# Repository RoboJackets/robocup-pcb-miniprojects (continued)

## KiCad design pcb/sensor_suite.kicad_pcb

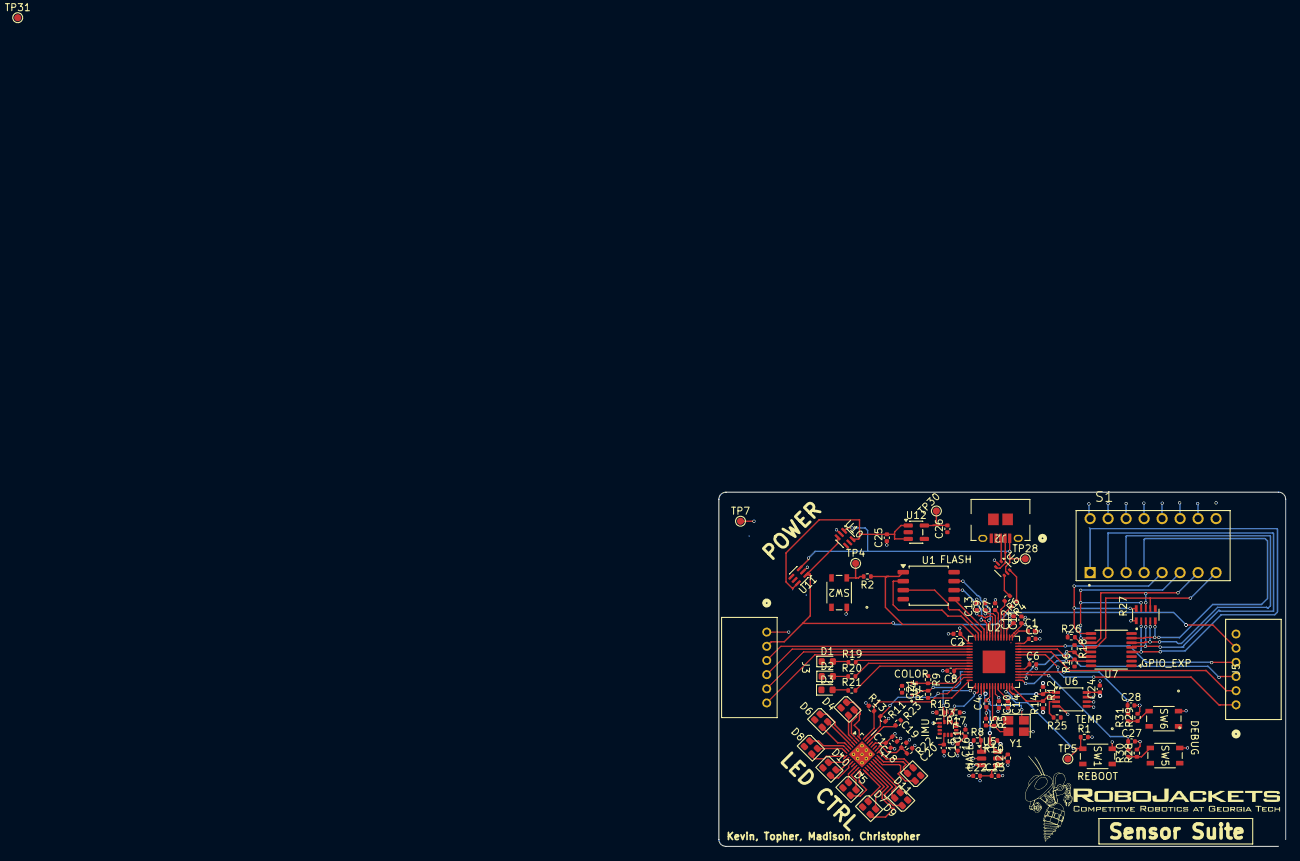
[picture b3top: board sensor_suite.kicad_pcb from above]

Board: 4 copper layers, 80.0 x 50.0 mm, 96 parts (0 on the bottom side), 91 nets.

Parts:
C1, C2, C3, C6, C7, C8, C9, C10, C13, C14, C27, C28: 100n; C_0402_1005Metric
C4, C5: 15p; C_0402_1005Metric
C11, C12, C18, C22, C25, C26: 1u; C_0402_1005Metric
C15: 10n; C_0402_1005Metric
C16: 2.2u; C_0402_1005Metric
C17, C19, C20, C21, C23, C24: 0.1u; C_0402_1005Metric
D1, D2, D3: RED; LED_0603_1608Metric
D4, D5, D6, D7, D8, D9, D10, D11: LED_RGB; LED_Cree-PLCC4_2x2mm_CW
IC1: IS31FL3254-QFLS4-TR; QFN-32-1EP_4x4mm_P0.4mm_EP2.65x2.65mm_ThermalVias
J2: USB_B_Micro; CONN_10118194-0001LF_AMP
J3, J5: Conn_01x06_Socket; CONN_S6B-PH-K-S_JST
R1, R28, R29, R30, R31: 10k; R_0402_1005Metric
R2, R5, R19, R20, R21: 1k; R_0402_1005Metric
R4, R6: 27.4; R_0402_1005Metric
R7, R8, R9, R10, R11, R12, R13, R14, R15, R16, R17, R18, R24, R25: 4.7k; R_0402_1005Metric
R22: 100k; R_0402_1005Metric
R23: 15k; R_0402_1005Metric
R26: 2k; R_0402_1005Metric
R27: YC158TJR-0710KL; RESCAXE64P320X160X70-10N
S1: DS01C-254-L-08BE; SW_DS01C-254-L-08BE
SW1, SW2, SW5, SW6: SKRPABE010; SW4_SKRPABE010_ALPS
TP4: ~{USB_Boot}; TestPoint_Pad_D1.0mm
TP5: ~{Reset}; TestPoint_Pad_D1.0mm
TP7: TestPoint; TestPoint_Pad_D1.0mm
TP28: +5V; TestPoint_Pad_D1.0mm
TP30: +3.3V; TestPoint_Pad_D1.0mm
TP31: VSPI; TestPoint_Pad_D1.0mm
U1: W25Q16JVSS; SOIC-8_5.3x5.3mm_P1.27mm
U2: RP2040; QFN-56-1EP_7x7mm_P0.4mm_EP3.2x3.2mm
U3: ICM-42605; LGA-14_3x2.5mm_P0.5mm_LayoutBorder3x4y
U4: VEML3328; SMD_L3328_VIS
U5: TMAG5273A2QDBV; SOT-23-6
U6: LM75ADP; TSSOP-8_3x3mm_P0.65mm
U7: TSSOP-16_4.4x5mm_P0.65mm
U9: USBLC6-2P6; SOT-666
U10, U11: LM66100DCK; SOT-363_SC-70-6
U12: AP2112K-3.3; SOT-23-5
Y1: ABM8-272-T3; Crystal_SMD_Abracon_ABM8AIG-4Pin_3.2x2.5mm

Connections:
+1.1V: C12.1, C13.1, C14.1, U2.23 (DVDD), U2.45 (VREG_VOUT), U2.50 (DVDD)
+3.3V: C1.1, C2.1, C3.1, C6.1, C7.1, C8.1, C9.1, C10.1, C11.1, C15.1, C16.1, C17.1, C21.1, C22.2, C23.1, C24.1, C26.2, D4.4 (BA), D5.4 (BA), D6.4 (BA), D7.4 (BA), D8.4 (BA), D9.4 (BA), D10.4 (BA), D11.4 (BA), R1.2, R7.1, R8.1, R9.1, R10.1, R11.1, R12.1, R13.1, R14.1, R15.1, R16.1, R17.1, R18.1, R24.1, R25.1, R26.1, R27.1, SW5.1 (A), SW6.1 (A), TP30.1 (1_1), U1.8 (VCC), U2.1 (IOVDD), U2.10 (IOVDD), U2.22 (IOVDD), U2.33 (IOVDD), U2.42 (IOVDD), U2.43 (ADC_AVDD), U2.44 (VREG_VIN), U2.48 (USB_VDD), U2.49 (IOVDD), U3.5 (VDDIO), U3.8 (VDD), U3.12 (CS), U4.4 (VDD), U5.4 (VCC), U6.8 (+Vs), U7.16 (VCC), U12.5 (VOUT)
+5V: C18.1, C19.1, IC1.28 (VCC)
/Color Sensor/I2C.SCL: R9.2, U2.12 (GPIO9), U4.3 (SCL)
/Color Sensor/I2C.SDA: R7.2, U2.11 (GPIO8), U4.2 (SDA)
/GPIO Expander/I2C.SCL: R18.2, U2.30 (GPIO19), U7.14 (SCL)
/GPIO Expander/I2C.SDA: R16.2, U2.29 (GPIO18), U7.15 (SDA)
/GPIO Expander/P0_PIN: R27.2 (R1), S1.1A, U7.4 (P0)
/GPIO Expander/P1_PIN: R27.3 (R2), S1.2A, U7.5 (P1)
/GPIO Expander/P2_PIN: R27.4 (R3), S1.3A, U7.6 (P2)
/GPIO Expander/P3_PIN: R27.5 (R4), S1.4A, U7.7 (P3)
/GPIO Expander/P4_PIN: R27.10 (R8), S1.5A, U7.9 (P4)
/GPIO Expander/P5_PIN: R27.9 (R7), S1.6A, U7.10 (P5)
/GPIO Expander/P6_PIN: R27.8 (R6), S1.7A, U7.11 (P6)
/GPIO Expander/P7_PIN: R27.7 (R5), S1.8A, U7.12 (P7)
/Hall Effect Sensor/I2C.SCL: R10.2, U2.18 (GPIO15), U5.6 (SDA)
/Hall Effect Sensor/I2C.SDA: R8.2, U2.17 (GPIO14), U5.1 (SCL)
/IMU/I2C.SCL: R17.2, U2.16 (GPIO13), U3.13 (SCL)
/IMU/I2C.SDA: R15.2, U2.15 (GPIO12), U3.14 (SDA)
/Indicator LEDs/ind_led0: R19.2, U2.7 (GPIO5)
/Indicator LEDs/ind_led1: R20.2, U2.8 (GPIO6)
/Indicator LEDs/ind_led2: R21.2, U2.9 (GPIO7)
/LED Controller/I2C.SCL: IC1.32 (SCL), R13.2, U2.14 (GPIO11)
/LED Controller/I2C.SDA: IC1.31 (SDA), R11.2, U2.13 (GPIO10)
/LED Controller/LED1.B: D4.3 (BK), IC1.3 (OUT3_B1)
/LED Controller/LED1.G: D4.2 (GK), IC1.2 (OUT2_G1)
/LED Controller/LED1.R: D4.1 (RK), IC1.1 (OUT1_R1)
/LED Controller/LED2.B: D6.3 (BK), IC1.6 (OUT6_B2)
/LED Controller/LED2.G: D6.2 (GK), IC1.5 (OUT5_G2)
/LED Controller/LED2.R: D6.1 (RK), IC1.4 (OUT4_R2)
/LED Controller/LED3.B: D8.3 (BK), IC1.9 (OUT9_B3)
/LED Controller/LED3.G: D8.2 (GK), IC1.8 (OUT8_G3)
/LED Controller/LED3.R: D8.1 (RK), IC1.7 (OUT7_R3)
/LED Controller/LED4.B: D10.3 (BK), IC1.12 (OUT12_B4)
/LED Controller/LED4.G: D10.2 (GK), IC1.11 (OUT11_G4)
/LED Controller/LED4.R: D10.1 (RK), IC1.10 (OUT10_R4)
/LED Controller/LED5.B: D5.3 (BK), IC1.16 (OUT15_B5)
/LED Controller/LED5.G: D5.2 (GK), IC1.15 (OUT14_G5)
/LED Controller/LED5.R: D5.1 (RK), IC1.14 (OUT13_R5)
/LED Controller/LED6.B: D7.3 (BK), IC1.19 (OUT18_B6)
/LED Controller/LED6.G: D7.2 (GK), IC1.18 (OUT17_G6)
/LED Controller/LED6.R: D7.1 (RK), IC1.17 (OUT16_R6)
/LED Controller/LED7.B: D9.3 (BK), IC1.22 (OUT21_B7)
/LED Controller/LED7.G: D9.2 (GK), IC1.21 (OUT20_G7)
/LED Controller/LED7.R: D9.1 (RK), IC1.20 (OUT19_R7)
/LED Controller/LED8.B: D11.3 (BK), IC1.25 (OUT24_B8)
/LED Controller/LED8.G: D11.2 (GK), IC1.24 (OUT23_G8)
/LED Controller/LED8.R: D11.1 (RK), IC1.23 (OUT22_R8)
/MCU/I2C_TS.SCL: R14.2, U2.28 (GPIO17), U6.2 (SCL)
/MCU/I2C_TS.SDA: R12.2, U2.27 (GPIO16), U6.1 (SDA)
/MCU/QSPI_CLK: U1.6 (CLK), U2.52 (QSPI_SCLK)
/MCU/QSPI_SD0: U1.5 (DI/IO_{0}), U2.53 (QSPI_SD0)
/MCU/QSPI_SD1: U1.2 (DO/IO_{1}), U2.55 (QSPI_SD1)
/MCU/QSPI_SD2: U1.3 (~WP/IO_{2}), U2.54 (QSPI_SD2)
/MCU/QSPI_SD3: U1.7 (~HOLD/~RESET/IO_{3}), U2.51 (QSPI_SD3)
/MCU/gp_btn_a: C27.1, R30.2, U2.31 (GPIO20)
/MCU/gp_btn_b: C28.1, R31.2, U2.32 (GPIO21)
/MCU/~QSPI_CS: R2.1, U1.1 (~CS), U2.56 (~QSPI_SS)
/MCU/~RESET: R1.1, SW1.2 (B), TP5.1 (1_1), U2.26 (RUN)
/MCU/~USB_BOOT: R2.2, SW2.2 (B), TP4.1 (1_1)
/Power/VSPI: J3.2, J5.5, TP31.1 (1_1), U10.3 (~CE), U11.1 (VIN)
/SPI0.CSN: J3.6, U2.5 (GPIO3)
/SPI0.MISO: J3.4, U2.3 (GPIO1)
/SPI0.MOSI: J3.5, U2.4 (GPIO2)
/SPI0.SCK: J3.3, U2.2 (GPIO0)
/SPI1.CSN: J5.1, U2.38 (GPIO26/ADC0)
/SPI1.MISO: J5.3, U2.40 (GPIO28/ADC2)
/SPI1.MOSI: J5.2, U2.39 (GPIO27/ADC1)
/SPI1.SCK: J5.4, U2.41 (GPIO29/ADC3)
/USB.DM: R4.1, U9.6 (I/O1)
/USB.DP: R6.1, U9.4 (I/O2)
GND: C1.2, C2.2, C3.2, C4.1, C5.1, C6.2, C7.2, C8.2, C9.2, C10.2, C11.2, C12.2, C13.2, C14.2, C15.2, C16.2, C17.2, C18.2, C19.2, C20.2, C21.2, C22.1, C23.2, C24.2, C25.1, C26.1, C27.2, C28.2, D1.1 (K), D2.1 (K), D3.1 (K), IC1.13 (GND_1), IC1.27 (AD), IC1.29 (GND_2), J2.5 (GND), J3.1, J5.6, R22.2, R23.2, R28.2, R29.2, S1.1B, S1.2B, S1.3B, S1.4B, S1.5B, S1.6B, S1.7B, S1.8B, SW1.1 (A), SW2.1 (A), TP7.1 (1_1), U1.4 (GND), U2.19 (TESTEN), U2.57 (GND), U3.1 (AD0), U3.6 (GND), U4.1 (GND), U5.2 (GND), U5.3 (TEST), U6.4 (GND), U6.5 (A2), U6.6 (A1), U6.7 (A0), U7.1 (A0), U7.2 (A1), U7.3 (A2), U7.8 (GND), U9.2 (GND), U10.2 (GND), U11.2 (GND), U12.2 (GND), Y1.2 (G), Y1.4 (G)
unnamed: C5.2, R5.2, Y1.3
unnamed: D1.2 (A), R19.1
unnamed: D2.2 (A), R20.1
unnamed: D3.2 (A), R21.1
unnamed: IC1.30 (ISET), R23.1
unnamed: C20.1, IC1.26 (SDB), R22.1
unnamed: J2.3 (D+), U9.1 (I/O1)
unnamed: J2.2 (D-), U9.3 (I/O2)
unnamed: J2.1 (VBUS), TP28.1 (1_1), U9.5 (VBUS), U10.1 (VIN), U11.3 (~CE)
unnamed: R28.1, R30.1, SW5.2 (B)
unnamed: R29.1, R31.1, SW6.2 (B)
unnamed: R4.2, U2.46 (USB_DM)
unnamed: R6.2, U2.47 (USB_DP)
unnamed: C4.2, U2.20 (XIN), Y1.1
unnamed: R5.1, U2.21 (XOUT)
unnamed: R24.2, U5.5 (~INT)
unnamed: R25.2, U6.3 (O.S.)
unnamed: R26.2, U7.13 (~INT)
VBUS: C25.2, U10.6 (VOUT), U11.6 (VOUT), U12.1 (VIN), U12.3 (EN)

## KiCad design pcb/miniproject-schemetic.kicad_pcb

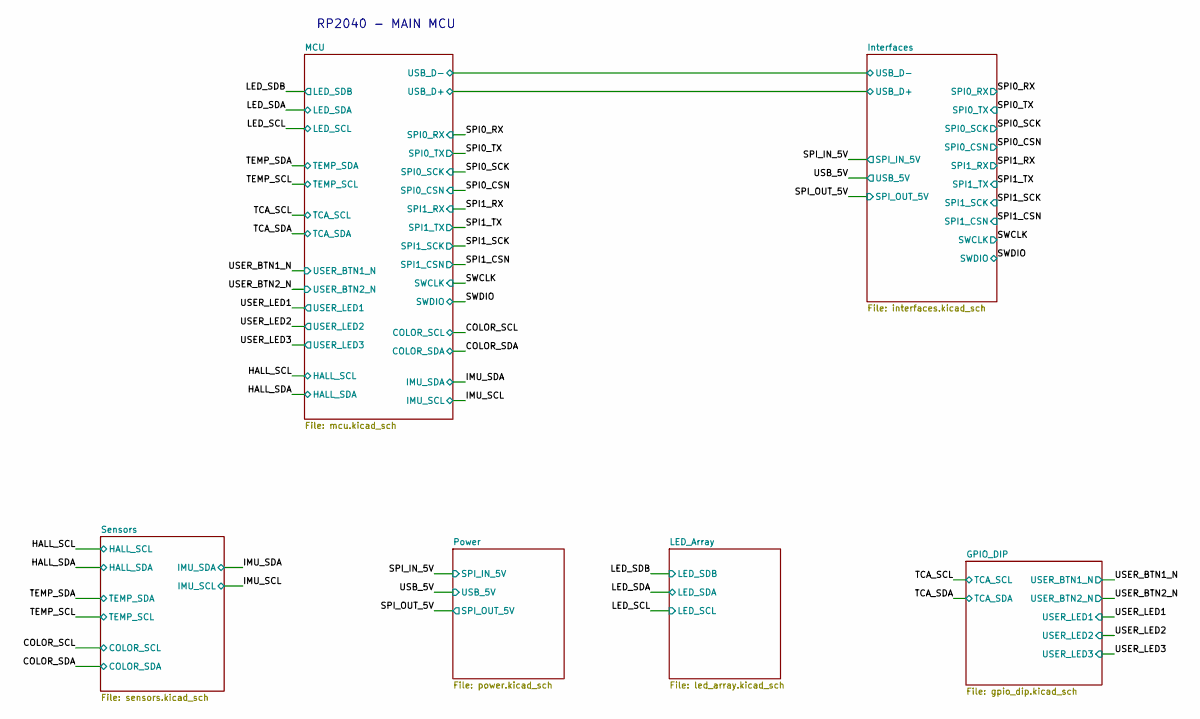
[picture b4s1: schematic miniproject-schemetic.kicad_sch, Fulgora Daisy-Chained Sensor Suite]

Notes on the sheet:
RP2040 - MAIN MCU

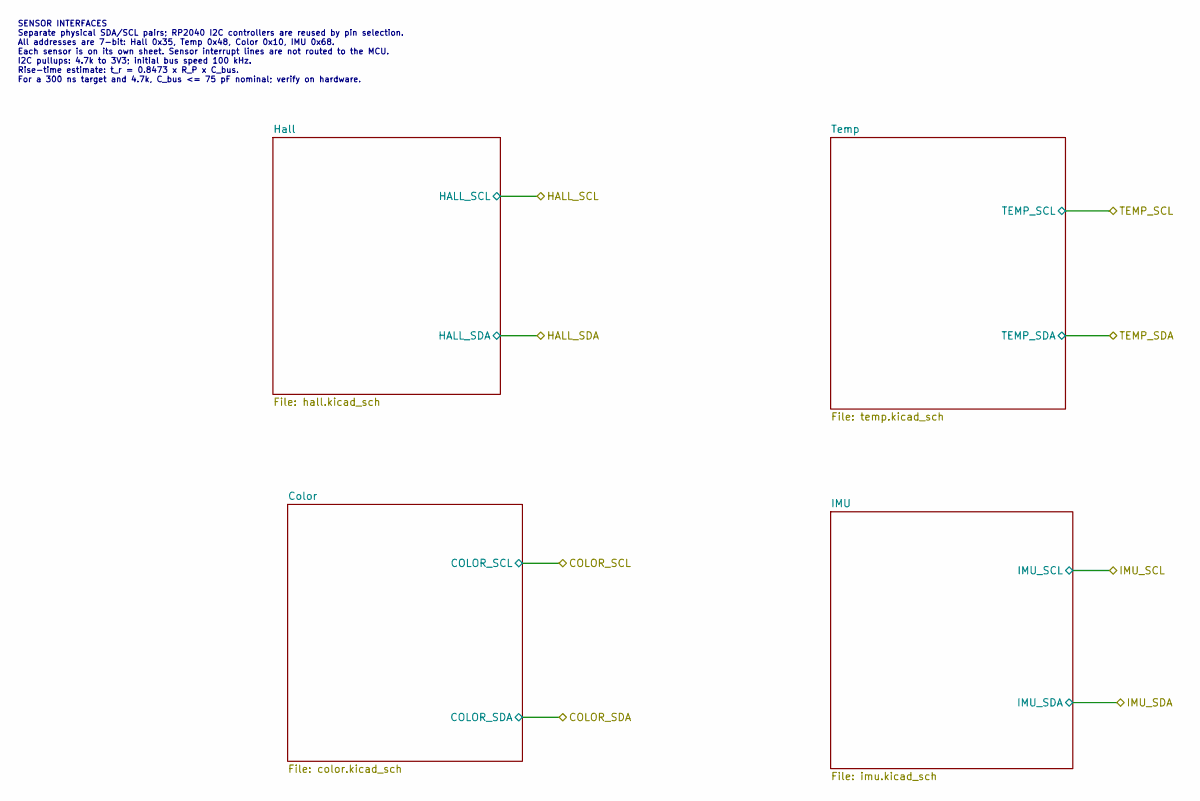
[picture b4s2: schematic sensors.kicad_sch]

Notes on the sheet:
SENSOR INTERFACES Separate physical SDA/SCL pairs; RP2040 I2C controllers are reused by pin selection. All addresses are 7-bit: Hall 0x35, Temp 0x48, Color 0x10, IMU 0x68. Each sensor is on its own sheet. Sensor interrupt lines are not routed to the MCU. I2C pullups: 4.7k to 3V3; initial bus speed 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

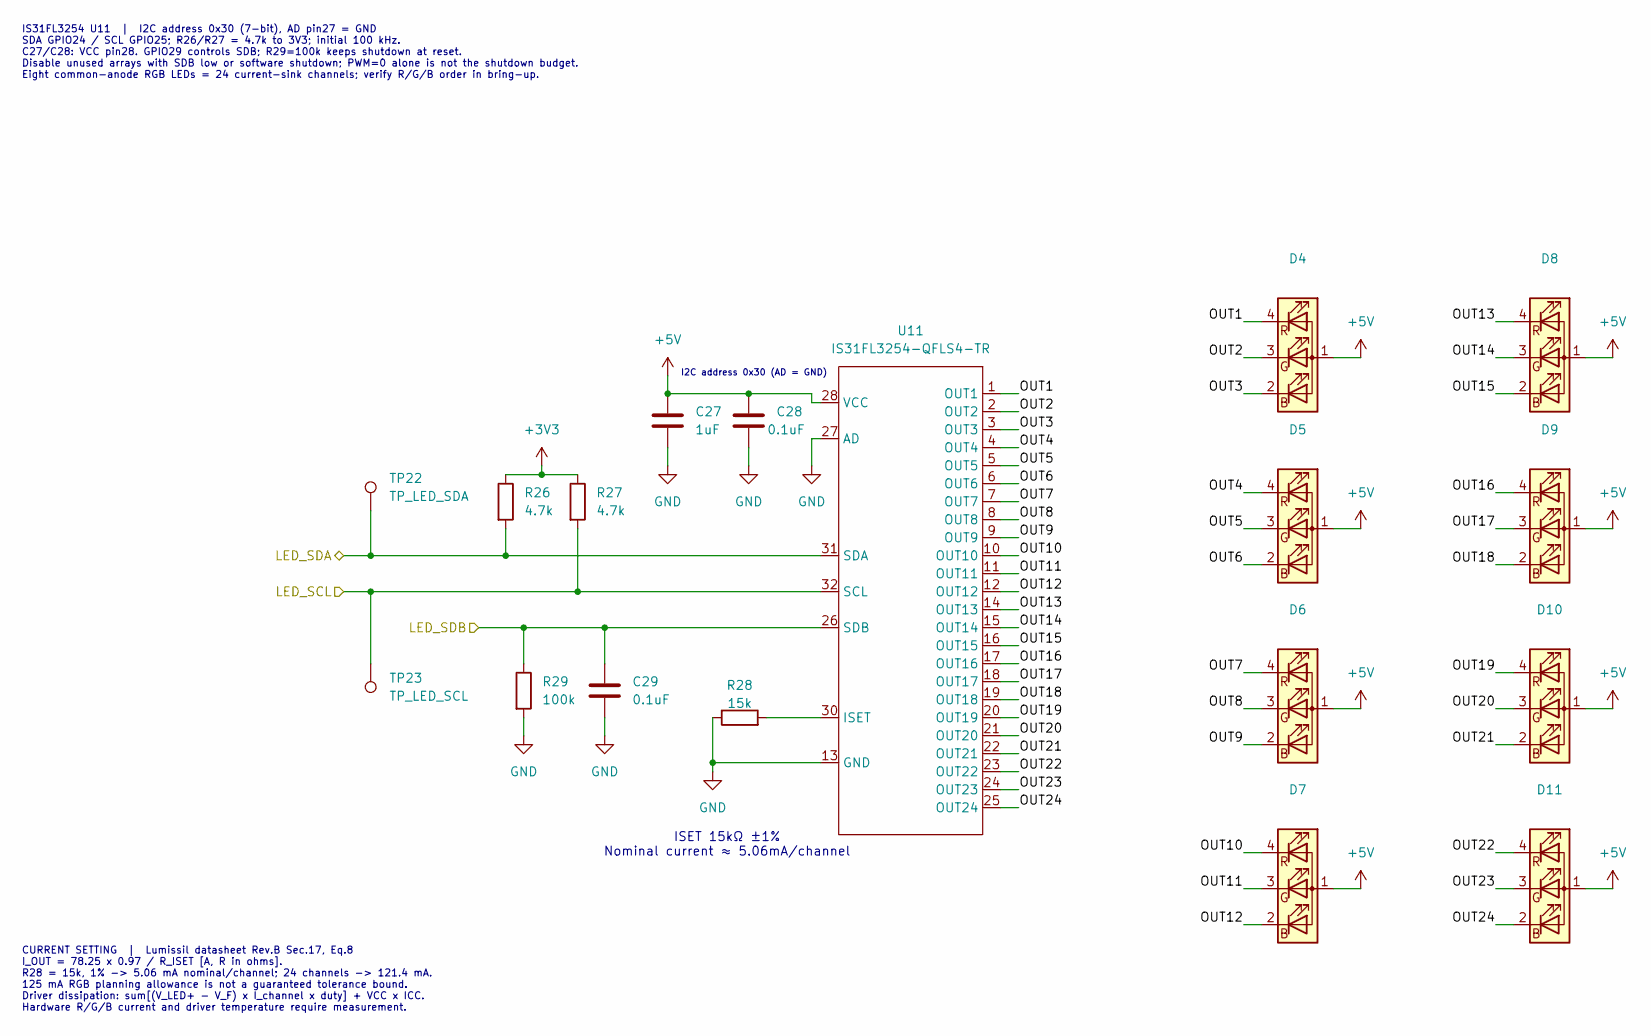
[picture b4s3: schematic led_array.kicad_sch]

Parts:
C27: 1uF; C_0603_1608Metric; Tolerance 10%; Voltage 10V minimum
C28: 0.1uF; C_0603_1608Metric; Tolerance 10%; Voltage 10V minimum
C29: 0.1uF; C_0603_1608Metric; Tolerance 10%; Voltage 6.3V minimum
D4, D5, D6, D7, D8, D9, D10, D11: CLMVC-FKA-CL1D1L71BB7C3C3; LED_Cree-PLCC4_2x2mm_CW
R26, R27: 4.7k; R_0603_1608Metric; Tolerance 1%
R28: 15k; R_0603_1608Metric; Tolerance 1%
R29: 100k; R_0603_1608Metric; Tolerance 1%
TP22: TP_LED_SDA; TestPoint_Pad_D1.0mm
TP23: TP_LED_SCL; TestPoint_Pad_D1.0mm
U11: IS31FL3254-QFLS4-TR; VQFN-32-1EP_4x4mm_P0.4mm_EP2.8x2.8mm

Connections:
+3V3: R26.1, R27.1; also elsewhere on the board
+5V: C27.1, C28.1, D4.1 (A), D5.1 (A), D6.1 (A), D7.1 (A), D8.1 (A), D9.1 (A), D10.1 (A), D11.1 (A), U11.28 (VCC); also elsewhere on the board
/LED_Array/OUT1: D4.4 (RK), U11.1 (OUT1)
/LED_Array/OUT2: D4.3 (GK), U11.2 (OUT2)
/LED_Array/OUT3: D4.2 (BK), U11.3 (OUT3)
/LED_Array/OUT4: D5.4 (RK), U11.4 (OUT4)
/LED_Array/OUT5: D5.3 (GK), U11.5 (OUT5)
/LED_Array/OUT6: D5.2 (BK), U11.6 (OUT6)
/LED_Array/OUT7: D6.4 (RK), U11.7 (OUT7)
/LED_Array/OUT8: D6.3 (GK), U11.8 (OUT8)
/LED_Array/OUT9: D6.2 (BK), U11.9 (OUT9)
/LED_Array/OUT10: D7.4 (RK), U11.10 (OUT10)
/LED_Array/OUT11: D7.3 (GK), U11.11 (OUT11)
/LED_Array/OUT12: D7.2 (BK), U11.12 (OUT12)
/LED_Array/OUT13: D8.4 (RK), U11.14 (OUT13)
/LED_Array/OUT14: D8.3 (GK), U11.15 (OUT14)
/LED_Array/OUT15: D8.2 (BK), U11.16 (OUT15)
/LED_Array/OUT16: D9.4 (RK), U11.17 (OUT16)
/LED_Array/OUT17: D9.3 (GK), U11.18 (OUT17)
/LED_Array/OUT18: D9.2 (BK), U11.19 (OUT18)
/LED_Array/OUT19: D10.4 (RK), U11.20 (OUT19)
/LED_Array/OUT20: D10.3 (GK), U11.21 (OUT20)
/LED_Array/OUT21: D10.2 (BK), U11.22 (OUT21)
/LED_Array/OUT22: D11.4 (RK), U11.23 (OUT22)
/LED_Array/OUT23: D11.3 (GK), U11.24 (OUT23)
/LED_Array/OUT24: D11.2 (BK), U11.25 (OUT24)
/LED_SCL: R27.2, TP23.1 (1_1), U11.32 (SCL); also elsewhere on the board
/LED_SDA: R26.2, TP22.1 (1_1), U11.31 (SDA); also elsewhere on the board
/LED_SDB: C29.1, R29.1, U11.26 (SDB); also elsewhere on the board
GND: C27.2, C28.2, C29.2, R28.1, R29.2, U11.13 (GND), U11.27 (AD), U11.29 (GND), U11.33 (GND_(pad)); also elsewhere on the board
unnamed: R28.2, U11.30 (ISET)

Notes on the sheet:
I2C address 0x30 (AD = GND)
ISET 15kΩ ±1% Nominal current ≈ 5.06mA/channel
IS31FL3254 U11 | I2C address 0x30 (7-bit), AD pin27 = GND SDA GPIO24 / SCL GPIO25; R26/R27 = 4.7k to 3V3; initial 100 kHz. C27/C28: VCC pin28. GPIO29 controls SDB; R29=100k keeps shutdown at reset. Disable unused arrays with SDB low or software shutdown; PWM=0 alone is not the shutdown budget. Eigh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
CURRENT SETTING | Lumissil datasheet Rev.B Sec.17, Eq.8 I_OUT = 78.25 x 0.97 / R_ISET [A, R in ohms]. R28 = 15k, 1% -> 5.06 mA nominal/channel; 24 channels -> 121.4 mA. 125 mA RGB planning allowance is not a guaranteed tolerance bound. Driver dissipation: sum[(V_LED+ - V_F) x I_channel x duty] + VC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

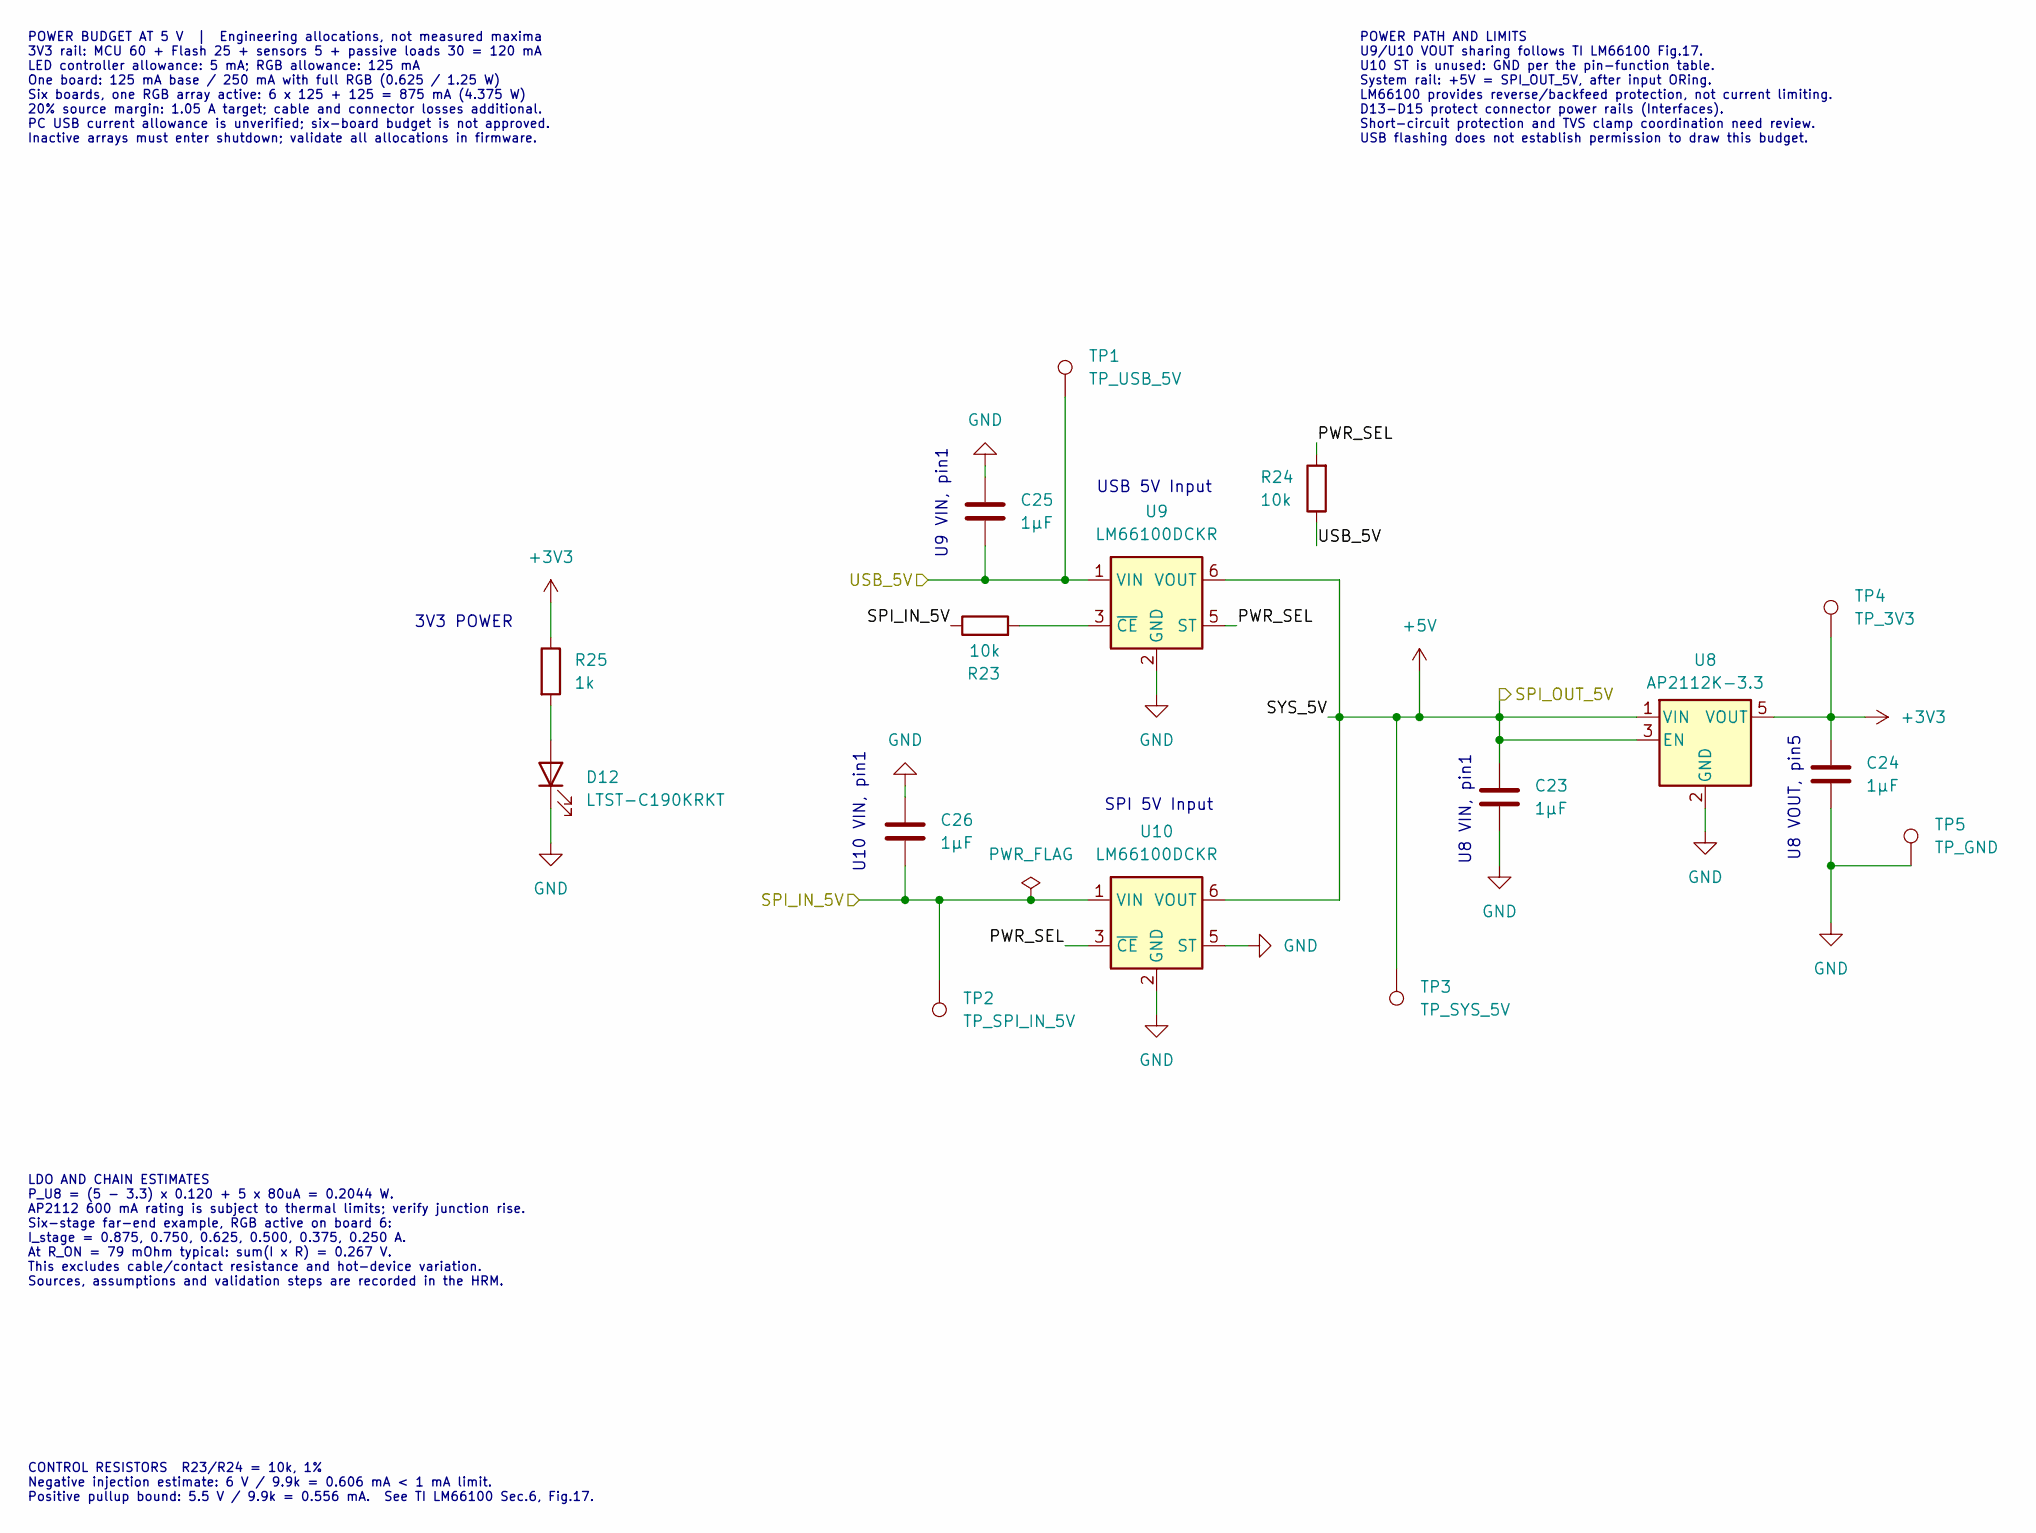
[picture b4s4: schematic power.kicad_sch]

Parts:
C23, C25, C26: 1µF; C_0603_1608Metric; Tolerance 10%; Voltage 10V minimum
C24: 1µF; C_0603_1608Metric; Tolerance 10%; Voltage 6.3V minimum
D12: LTST-C190KRKT; LED_0603_1608Metric
R23, R24: 10k; R_0603_1608Metric; Tolerance 1%
R25: 1k; R_0603_1608Metric; Tolerance 1%
TP1: TP_USB_5V; TestPoint_Pad_D1.0mm
TP2: TP_SPI_IN_5V; TestPoint_Pad_D1.0mm
TP3: TP_SYS_5V; TestPoint_Pad_D1.0mm
TP4: TP_3V3; TestPoint_Pad_D1.0mm
TP5: TP_GND; TestPoint_Pad_D1.0mm
U8: AP2112K-3.3; SOT-23-5
U9, U10: LM66100DCKR; SOT-363_SC-70-6

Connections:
+3V3: C24.1, R25.1, TP4.1 (1_1), U8.5 (VOUT); also elsewhere on the board
+5V: C23.1, TP3.1 (1_1), U8.1 (VIN), U8.3 (EN), U9.6 (VOUT), U10.6 (VOUT); also elsewhere on the board
/Power/PWR_SEL: R24.2, U9.5 (ST), U10.3 (~CE)
/SPI_IN_5V: C26.2, R23.1, TP2.1 (1_1), U10.1 (VIN); also elsewhere on the board
/USB_5V: C25.2, R24.1, TP1.1 (1_1), U9.1 (VIN); also elsewhere on the board
GND: C23.2, C24.2, C25.1, C26.1, D12.1 (K), TP5.1 (1_1), U8.2 (GND), U9.2 (GND), U10.2 (GND), U10.5 (ST); also elsewhere on the board
unnamed: D12.2 (A), R25.2
unnamed: R23.2, U9.3 (~CE)

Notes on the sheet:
3V3 POWER
SPI 5V Input
USB 5V Input
U9 VIN, pin1
U8 VOUT, pin5
U8 VIN, pin1
U10 VIN, pin1
POWER BUDGET AT 5 V | Engineering allocations, not measured maxima 3V3 rail: MCU 60 + Flash 25 + sensors 5 + passive loads 30 = 120 mA LED controller allowance: 5 mA; RGB allowance: 125 mA One board: 125 mA base / 250 mA with full RGB (0.625 / 1.25 W) Six boards, one RGB array active: 6 x 125 + 125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
POWER PATH AND LIMITS U9/U10 VOUT sharing follows TI LM66100 Fig.17. U10 ST is unused: GND per the pin-function table. System rail: +5V = SPI_OUT_5V, after input ORing. LM66100 provides reverse/backfeed protection, not current limiting. D13-D15 protect connector power rails (Interfaces). Short-circ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
LDO AND CHAIN ESTIMATES P_U8 = (5 - 3.3) x 0.120 + 5 x 80uA = 0.2044 W. AP2112 600 mA rating is subject to thermal limits; verify junction rise. Six-stage far-end example, RGB active on board 6: I_stage = 0.875, 0.750, 0.625, 0.500, 0.375, 0.250 A. At R_ON = 79 mOhm typical: sum(I x R) = 0.267 V. T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
CONTROL RESISTORS R23/R24 = 10k, 1% Negative injection estimate: 6 V / 9.9k = 0.606 mA < 1 mA limit. Positive pullup bound: 5.5 V / 9.9k = 0.556 mA. See TI LM66100 Sec.6, Fig.17.

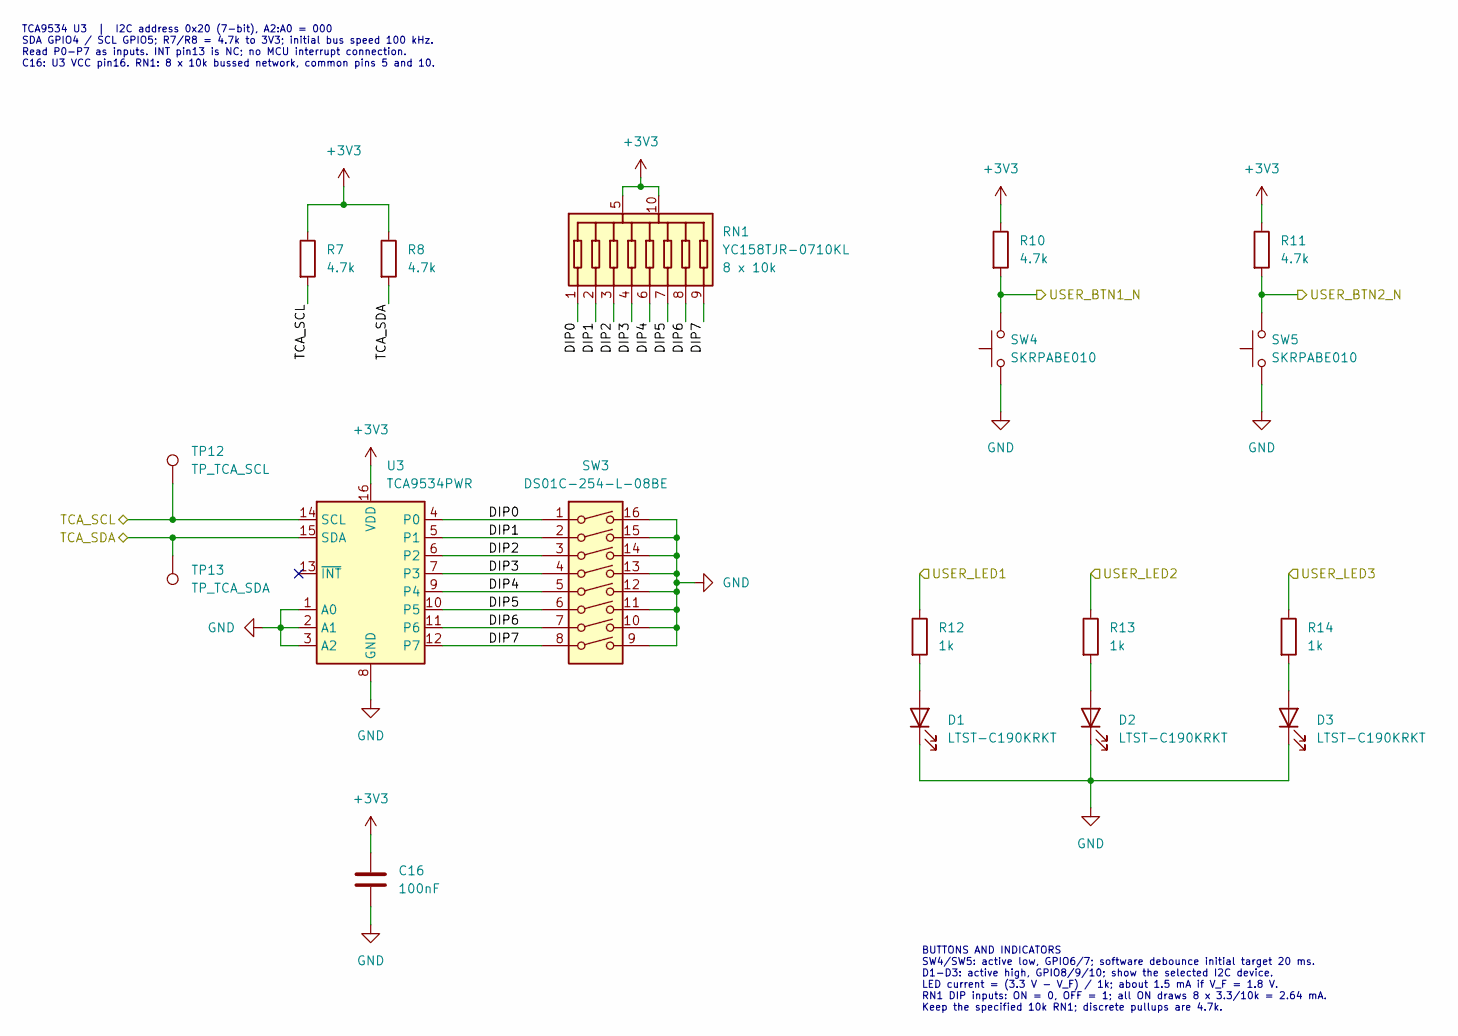
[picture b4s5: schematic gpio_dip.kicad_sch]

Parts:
C16: 100nF; C_0603_1608Metric; Tolerance 10%; Voltage 6.3V minimum
D1, D2, D3: LTST-C190KRKT; LED_0603_1608Metric
R7, R8, R10, R11: 4.7k; R_0603_1608Metric; Tolerance 1%
R12, R13, R14: 1k; R_0603_1608Metric; Tolerance 1%
RN1: YC158TJR-0710KL; Yageo_YC158T_10Pin_3.2x1.6mm_P0.64mm; Tolerance 5%
SW3: DS01C-254-L-08BE; SW_DIP_SPSTx08_SameSky_DS01C-254-L-08BE
SW4, SW5: SKRPABE010; SW_SPST_ALPS_SKRPABE010_4.2x3.2mm
TP12: TP_TCA_SCL; TestPoint_Pad_D1.0mm
TP13: TP_TCA_SDA; TestPoint_Pad_D1.0mm
U3: TCA9534PWR; TSSOP-16_4.4x5mm_P0.65mm

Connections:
+3V3: C16.1, R7.1, R8.1, R10.1, R11.1, RN1.5 (COM), RN1.10 (COM), U3.16 (VDD); also elsewhere on the board
/GPIO_DIP/DIP0: RN1.1 (R1), SW3.1, U3.4 (P0)
/GPIO_DIP/DIP1: RN1.2 (R2), SW3.2, U3.5 (P1)
/GPIO_DIP/DIP2: RN1.3 (R3), SW3.3, U3.6 (P2)
/GPIO_DIP/DIP3: RN1.4 (R4), SW3.4, U3.7 (P3)
/GPIO_DIP/DIP4: RN1.6 (R5), SW3.5, U3.9 (P4)
/GPIO_DIP/DIP5: RN1.7 (R6), SW3.6, U3.10 (P5)
/GPIO_DIP/DIP6: RN1.8 (R7), SW3.7, U3.11 (P6)
/GPIO_DIP/DIP7: RN1.9 (R8), SW3.8, U3.12 (P7)
/TCA_SCL: R7.2, TP12.1 (1_1), U3.14 (SCL); also elsewhere on the board
/TCA_SDA: R8.2, TP13.1 (1_1), U3.15 (SDA); also elsewhere on the board
/USER_BTN1_N: R10.2, SW4.2; also elsewhere on the board
/USER_BTN2_N: R11.2, SW5.2; also elsewhere on the board
/USER_LED1: R12.1; also elsewhere on the board
/USER_LED2: R13.1; also elsewhere on the board
/USER_LED3: R14.1; also elsewhere on the board
GND: C16.2, D1.1 (K), D2.1 (K), D3.1 (K), SW3.9, SW3.10, SW3.11, SW3.12, SW3.13, SW3.14, SW3.15, SW3.16, SW4.1, SW5.1, U3.1 (A0), U3.2 (A1), U3.3 (A2), U3.8 (GND); also elsewhere on the board
unnamed: D1.2 (A), R12.2
unnamed: D2.2 (A), R13.2
unnamed: D3.2 (A), R14.2

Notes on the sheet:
TCA9534 U3 | I2C address 0x20 (7-bit), A2:A0 = 000 SDA GPIO4 / SCL GPIO5; R7/R8 = 4.7k to 3V3; initial bus speed 100 kHz. Read P0-P7 as inputs. INT pin13 is NC; no MCU interrupt connection. C16: U3 VCC pin16. RN1: 8 x 10k bussed network, common pins 5 and 10.
BUTTONS AND INDICATORS SW4/SW5: active low, GPIO6/7; software debounce initial target 20 ms. D1-D3: active high, GPIO8/9/10; show the selected I2C device. LED current = (3.3 V - V_F) / 1k; about 1.5 mA if V_F = 1.8 V. RN1 DIP inputs: ON = 0, OFF = 1; all ON draws 8 x 3.3/10k = 2.64 mA. Keep the spe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

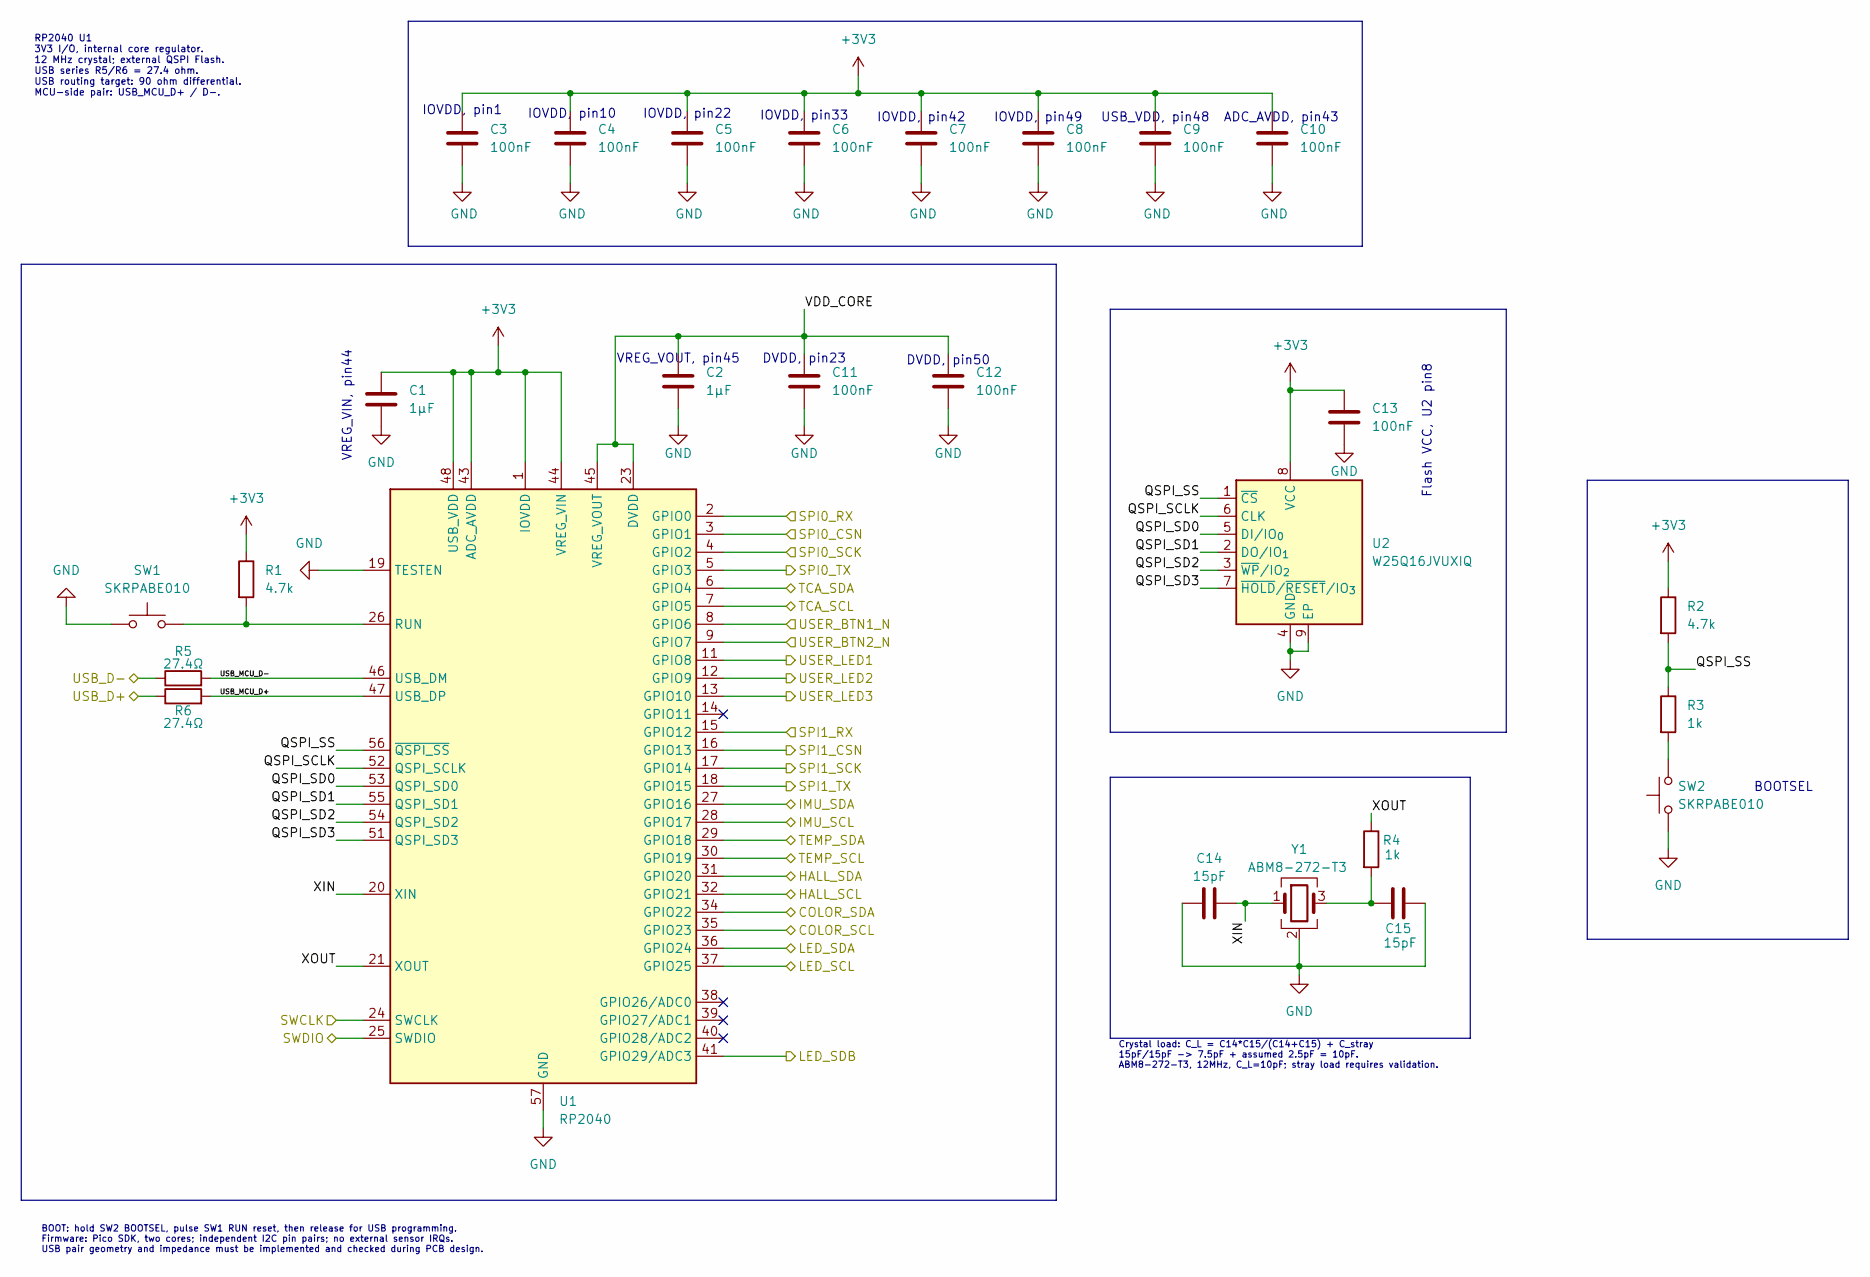
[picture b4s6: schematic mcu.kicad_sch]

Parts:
C1, C2: 1µF; C_0603_1608Metric; Tolerance 10%; Voltage 6.3V minimum
C3, C4, C5, C6, C7, C8, C9, C10, C11, C12, C13: 100nF; C_0603_1608Metric; Tolerance 10%; Voltage 6.3V minimum
C14, C15: 15pF; C_0603_1608Metric; Tolerance 5%; Voltage 6.3V minimum
R1, R2: 4.7k; R_0603_1608Metric; Tolerance 1%
R3, R4: 1k; R_0603_1608Metric; Tolerance 1%
R5, R6: 27.4Ω; R_0603_1608Metric; Tolerance 1%
SW1, SW2: SKRPABE010; SW_SPST_ALPS_SKRPABE010_4.2x3.2mm
U1: RP2040; QFN-56-1EP_7x7mm_P0.4mm_EP3.2x3.2mm
U2: W25Q16JVUXIQ; Winbond_USON-8-1EP_3x2mm_P0.5mm_EP0.2x1.6mm
Y1: ABM8-272-T3; Crystal_SMD_3225-4Pin_3.2x2.5mm

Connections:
+3V3: C1.1, C3.1, C4.1, C5.1, C6.1, C7.1, C8.1, C9.1, C10.1, C13.1, R1.1, R2.1, U1.1 (IOVDD), U1.10 (IOVDD), U1.22 (IOVDD), U1.33 (IOVDD), U1.42 (IOVDD), U1.43 (ADC_AVDD), U1.44 (VREG_VIN), U1.48 (USB_VDD), U1.49 (IOVDD), U2.8 (VCC); also elsewhere on the board
/COLOR_SCL: U1.35 (GPIO23); also elsewhere on the board
/COLOR_SDA: U1.34 (GPIO22); also elsewhere on the board
/HALL_SCL: U1.32 (GPIO21); also elsewhere on the board
/HALL_SDA: U1.31 (GPIO20); also elsewhere on the board
/IMU_SCL: U1.28 (GPIO17); also elsewhere on the board
/IMU_SDA: U1.27 (GPIO16); also elsewhere on the board
/Interfaces/USB_D+: R6.1; also elsewhere on the board
/Interfaces/USB_D-: R5.1; also elsewhere on the board
/LED_SCL: U1.37 (GPIO25); also elsewhere on the board
/LED_SDA: U1.36 (GPIO24); also elsewhere on the board
/LED_SDB: U1.41 (GPIO29/ADC3); also elsewhere on the board
/MCU/QSPI_SCLK: U1.52 (QSPI_SCLK), U2.6 (CLK)
/MCU/QSPI_SD0: U1.53 (QSPI_SD0), U2.5 (DI/IO_{0})
/MCU/QSPI_SD1: U1.55 (QSPI_SD1), U2.2 (DO/IO_{1})
/MCU/QSPI_SD2: U1.54 (QSPI_SD2), U2.3 (~WP/IO_{2})
/MCU/QSPI_SD3: U1.51 (QSPI_SD3), U2.7 (~HOLD/~RESET/IO_{3})
/MCU/QSPI_SS: R2.2, R3.1, U1.56 (~QSPI_SS), U2.1 (~CS)
/MCU/USB_MCU_D+: R6.2, U1.47 (USB_DP)
/MCU/USB_MCU_D-: R5.2, U1.46 (USB_DM)
/MCU/VDD_CORE: C2.1, C11.1, C12.1, U1.23 (DVDD), U1.45 (VREG_VOUT), U1.50 (DVDD)
/MCU/XIN: C14.2, U1.20 (XIN), Y1.1
/MCU/XOUT: R4.1, U1.21 (XOUT)
/SPI0_CSN: U1.3 (GPIO1); also elsewhere on the board
/SPI0_RX: U1.2 (GPIO0); also elsewhere on the board
/SPI0_SCK: U1.4 (GPIO2); also elsewhere on the board
/SPI0_TX: U1.5 (GPIO3); also elsewhere on the board
/SPI1_CSN: U1.16 (GPIO13); also elsewhere on the board
/SPI1_RX: U1.15 (GPIO12); also elsewhere on the board
/SPI1_SCK: U1.17 (GPIO14); also elsewhere on the board
/SPI1_TX: U1.18 (GPIO15); also elsewhere on the board
/SWCLK: U1.24 (SWCLK); also elsewhere on the board
/SWDIO: U1.25 (SWDIO); also elsewhere on the board
/TCA_SCL: U1.7 (GPIO5); also elsewhere on the board
/TCA_SDA: U1.6 (GPIO4); also elsewhere on the board
/TEMP_SCL: U1.30 (GPIO19); also elsewhere on the board
/TEMP_SDA: U1.29 (GPIO18); also elsewhere on the board
/USER_BTN1_N: U1.8 (GPIO6); also elsewhere on the board
/USER_BTN2_N: U1.9 (GPIO7); also elsewhere on the board
/USER_LED1: U1.11 (GPIO8); also elsewhere on the board
/USER_LED2: U1.12 (GPIO9); also elsewhere on the board
/USER_LED3: U1.13 (GPIO10); also elsewhere on the board
GND: C1.2, C2.2, C3.2, C4.2, C5.2, C6.2, C7.2, C8.2, C9.2, C10.2, C11.2, C12.2, C13.2, C14.1, C15.2, SW1.1, SW2.1, U1.19 (TESTEN), U1.57 (GND), U2.4 (GND), U2.9 (EP), Y1.2 (G), Y1.4 (G); also elsewhere on the board
unnamed: C15.1, R4.2, Y1.3
unnamed: R3.2, SW2.2
unnamed: R1.2, SW1.2, U1.26 (RUN)

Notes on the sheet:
DVDD, pin23
VREG_VIN, pin44
IOVDD, pin49
IOVDD, pin42
Flash VCC, U2 pin8
ADC_AVDD, pin43
DVDD, pin50
IOVDD, pin10
USB_VDD, pin48
IOVDD, pin33
IOVDD, pin22
BOOTSEL
IOVDD, pin1
VREG_VOUT, pin45
RP2040 U1 3V3 I/O, internal core regulator. 12 MHz crystal; external QSPI Flash. USB series R5/R6 = 27.4 ohm. USB routing target: 90 ohm differential. MCU-side pair: USB_MCU_D+ / D-.
Crystal load: C_L = C14*C15/(C14+C15) + C_stray 15pF/15pF -> 7.5pF + assumed 2.5pF = 10pF. ABM8-272-T3, 12MHz, C_L=10pF; stray load requires validation.
BOOT: hold SW2 BOOTSEL, pulse SW1 RUN reset, then release for USB programming. Firmware: Pico SDK, two cores; independent I2C pin pairs; no external sensor IRQs. USB pair geometry and impedance must be implemented and checked during PCB design.
